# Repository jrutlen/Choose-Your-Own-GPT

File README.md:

# Choose Your Own GPT

Choose Your Own GPT is a seemingly analog device without any screens or visible digital elements. Spinning the physical dials to select characters and a story setting and then hitting the large arcade 'go' button, the built-in printer will spit out a Choose Your Own Adventure type story on the built-in receipt printer.

## Features

- Built-in 58mm thermal printer to dispense stories on demand
- Designed to be printable on 200mm² 3D printers
- Top dials can be snapped off of the main PCB to allow modification to any size
- Optional 4th dial can be added to increase story objects or add an additional element (talk like a pirate, etc.)
- Support for e-ink display (untested)
- Over-the-air (OTA) firmware updates via the web portal
- Import/export configuration as JSON

## Hardware Requirements

- ESP32 development board
- 58mm thermal printer (connected to ESP32 Serial2: RX=16, TX=17)
- Adafruit NeoPixel LEDs (WaitEnd ring: 13 LEDs on pin 26; Go button: 3 LEDs on pin 33)
- Arcade-style buttons with LEDs (Red: pin 27, Blue: pin 12, Green: pin 2, Yellow: pin 15)
- Rotary dials wired to input matrix (see PCB directory for schematic)
- 3D-printed enclosure (STL files in the `STLs` directory)
- Bill of materials in `Bill of Materials.csv`

## Building and Flashing

This project uses [PlatformIO](https://platformio.org/). All library dependencies are declared in `ChooseYourOwnGPT/platformio.ini` and are fetched automatically on first build.

1. Install [PlatformIO IDE](https://platformio.org/install) or the PlatformIO CLI.
2. Open the `ChooseYourOwnGPT` folder as a PlatformIO project.
3. Build and upload to the ESP32:
   ```
   pio run --target upload
   ```
4. You do **not** need to add your API key to the code before uploading — it is set via the web portal after the device is running.

### Library Dependencies

| Library | Version |
|---------|---------|
| Adafruit NeoPixel | 1.12.4 |
| Adafruit Thermal Printer | 1.4.1 |
| NetWizard | 1.2.0 |
| ArduinoJson | 7.3.1 |

### Building with GitHub Actions

A workflow (`.github/workflows/build.yml`) automatically builds the firmware on every push or pull request to `main`/`master` that touches `ChooseYourOwnGPT/` or the workflow file itself. No local toolchain is required to produce a flashable binary.

**What the workflow does:**
1. Checks out the repository.
2. Installs PlatformIO via `pip`.
3. Runs `pio run` inside `ChooseYourOwnGPT/`.
4. Uploads the compiled binaries as a `firmware` artifact:
   - `firmware.bin` — application image
   - `bootloader.bin` — ESP32 bootloader
   - `partitions.bin` — partition table

**Downloading the artifact:**
1. Go to the **Actions** tab of the repository on GitHub.
2. Click the latest successful **Build Firmware** run.
3. Scroll to the **Artifacts** section at the bottom and download `firmware`.
4. Unzip the archive to get the `.bin` files.

**Flashing the downloaded firmware:**

To flash from scratch (first time or full reflash), use `esptool.py`:
```
esptool.py --chip esp32 --baud 921600 \
  write_flash \
  0x1000  bootloader.bin \
  0x8000  partitions.bin \
  0x10000 firmware.bin
```

To update an already-running device, use the OTA firmware update in the web portal — see [OTA Firmware Update](#ota-firmware-update) below.

## First-Time Setup

1. Power on the device. It will start a Wi-Fi access point named **`ChooseYourOwnGPT`** with the password **`itMightBeMagic`**.
2. Connect to that network from your phone or computer.
3. A captive portal will open automatically (or navigate to `http://192.168.4.1`).
4. Enter your home Wi-Fi credentials and save. The device will reboot and connect to your network.

## Configuration

Once the device is connected to your Wi-Fi network, open a browser and go to:

```
http://<device-ip>/config
```

The device IP is printed to the serial console on connection. The configuration portal lets you adjust all settings without reflashing.

### General Settings

| Setting | Description |
|---------|-------------|
| **OpenAI API Key** | Your `sk-…` key from [platform.openai.com](https://platform.openai.com/api-keys). Stored on the device only — never sent anywhere except the OpenAI API. |
| **OpenAI Model** | The model to use for story generation (default: `gpt-4o`). |
| **Hyphenate long words** | When enabled, words that are too long for a line are broken with a hyphen instead of overflowing. |

### Character Names (Small Dial)

Up to **10** character names can be assigned to positions on the small dial. Each position corresponds to a dial setting (0–9). Names can include relationship context (e.g. `"Mia (a 7-year-old girl)"`), which is passed directly to the story prompt.

### Adventure Destinations (Large Dial)

Up to **16** adventure destinations can be assigned to positions on the large dial. Each entry is a sentence fragment appended to the story prompt (e.g. `" who go on an adventure in the Amazon Rainforest."`).

### Story Prompts

These fields control the text sent to the OpenAI API at each stage of the story:

| Field | Description |
|-------|-------------|
| **Story Prompt** | Opening prompt prepended before the selected character names. |
| **Instructions** | Instructions appended after the adventure destination (formatting rules, chapter length, button options, etc.). |
| **Surprise Ending Prompt** | Sent when the red button is pressed to request an unexpected ending. |
| **Blue Button – Continue** | Message sent when the blue button is pressed to continue the story. |
| **Blue Button – Final Chapter** | Message sent when the blue button is pressed in the final chapter. |
| **Yellow Button – Continue** | Message sent when the yellow button is pressed to continue the story. |
| **Yellow Button – Final Chapter** | Message sent when the yellow button is pressed in the final chapter. |

### Import / Export

Use the **Export Settings JSON** button to download all current settings as a `cyogpt-config.json` file. Use **Import Settings JSON** to restore or share a configuration.

### OTA Firmware Update

The `/config` portal includes a firmware update section. Select a compiled `.bin` file (from `pio run` build output) and click **Upload Firmware**. The device will reboot automatically after a successful update.

## Usage

1. Power on the device and wait for it to connect to Wi-Fi (the LEDs will indicate status).
2. Spin the **small dial** to select a character and the **large dial** to choose an adventure destination.
3. Press the **green Go button** to generate a story. The printer will output the first chapter.
4. At the end of each chapter, press the **blue** or **yellow** button to choose how the story continues.
5. Press the **red button** at any point to trigger a surprise ending.
6. After the final (5th) chapter, the story is complete. Set the dials and press Go to start a new story.

## Network Printing

The device also works as a simple network printer. It listens on TCP port **9100** and forwards every byte it receives, unchanged, to the thermal printer. A job ends when the client closes the connection or sends nothing for 3 seconds. After each job the printer's text formatting is reset, so stories print normally afterwards.

Jobs are handled between story steps. While a chapter is generating or printing, the sender waits until the device is free.

Quick test from any machine on the network:
```
echo "Hello from the network" | nc -q 5 <device-ip> 9100
```

### Python client

`clients/python/cyogpt_printer.py` is a single-file client that builds the printer's command bytes. Plain text and ASCII-art glyphs need only the standard library. Printing images or rendering TrueType text needs [Pillow](https://pypi.org/project/pillow/) (`pip install pillow`).

```python
from cyogpt_printer import Printer

HEART = [
    ".##...##.",
    "####.####",
    "#########",
    ".#######.",
    "..#####..",
    "...###...",
    "....#....",
]

with Printer("192.168.1.50") as p:          # sent as one job when the block exits
    p.justify("C").size("L").bold().text("Hello!").bold(False).size("S")
    p.glyph(HEART, scale=6, align="C")      # ASCII-art glyph, each pixel 6x6 dots
    p.render_text("☀ 21°C ☂", font_path="/usr/share/fonts/truetype/dejavu/DejaVuSans.ttf")
    p.image("logo.png")                     # scaled to 384 px and dithered
    p.justify("L").text("Printed from a Raspberry Pi")
    p.feed(3)
```

| Method | Description |
|--------|-------------|
| `text(s)` / `write(s)` | Text with or without a newline (32 chars per line at size S, encoded as CP437) |
| `bold()`, `underline(0-2)`, `inverse()`, `size('S'/'M'/'L')`, `justify('L'/'C'/'R')`, `line_height(dots)` | Text styles |
| `feed(n)` | Feed *n* lines |
| `glyph(rows, scale, align)` | Print ASCII-art (`#` = black) as a bitmap |
| `bitmap(w, h, data, align)` | Print a raw 1-bit bitmap (MSB-first rows, 1 = black, max 384 px wide) |
| `image(path_or_pil, align)` | Print an image (needs Pillow) |
| `render_text(s, font_path, font_size, align)` | Draw any Unicode text or symbol with a font (needs Pillow) |
| `raw(bytes)` | Send arbitrary printer command bytes |

It can also be run from the command line:
```
python cyogpt_printer.py <device-ip> "Some text" --center --size M
python cyogpt_printer.py <device-ip> --image photo.jpg
```

> Anyone on your local network can print to the device. There is no authentication.

### Idle LEDs

While the box waits for a story, its dial LEDs breathe. A device that borrows the printer can switch that off, say while the box stands in a dark room as part of something else, and back on again:

```
curl -X POST http://<device-ip>/api/leds -d '{"idle": false}'   # dark while idle
curl -X POST http://<device-ip>/api/leds -d '{"idle": true}'    # breathing again
curl http://<device-ip>/api/leds                                 # {"idle":true}
```

Turning a dial still lights its LED, and a story runs exactly as usual. The setting is not saved: the box always starts with the LEDs on.

## Related

Build log with photos

[Hackaday.io](https://hackaday.io/project/192751-choose-your-own-gpt)

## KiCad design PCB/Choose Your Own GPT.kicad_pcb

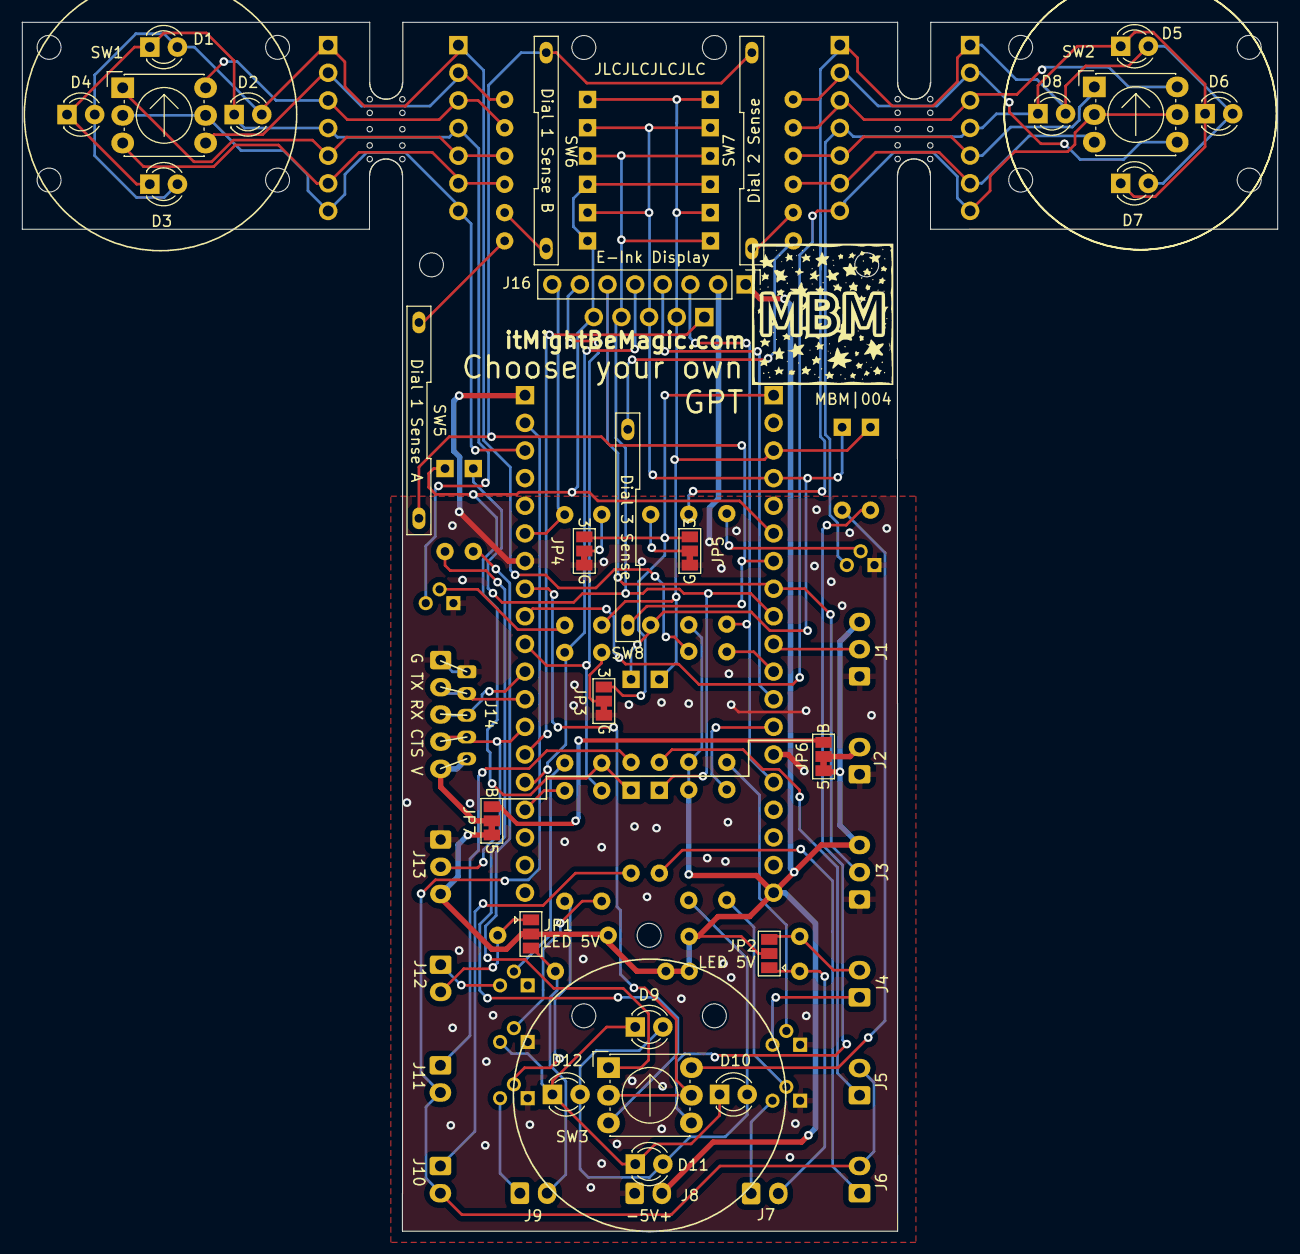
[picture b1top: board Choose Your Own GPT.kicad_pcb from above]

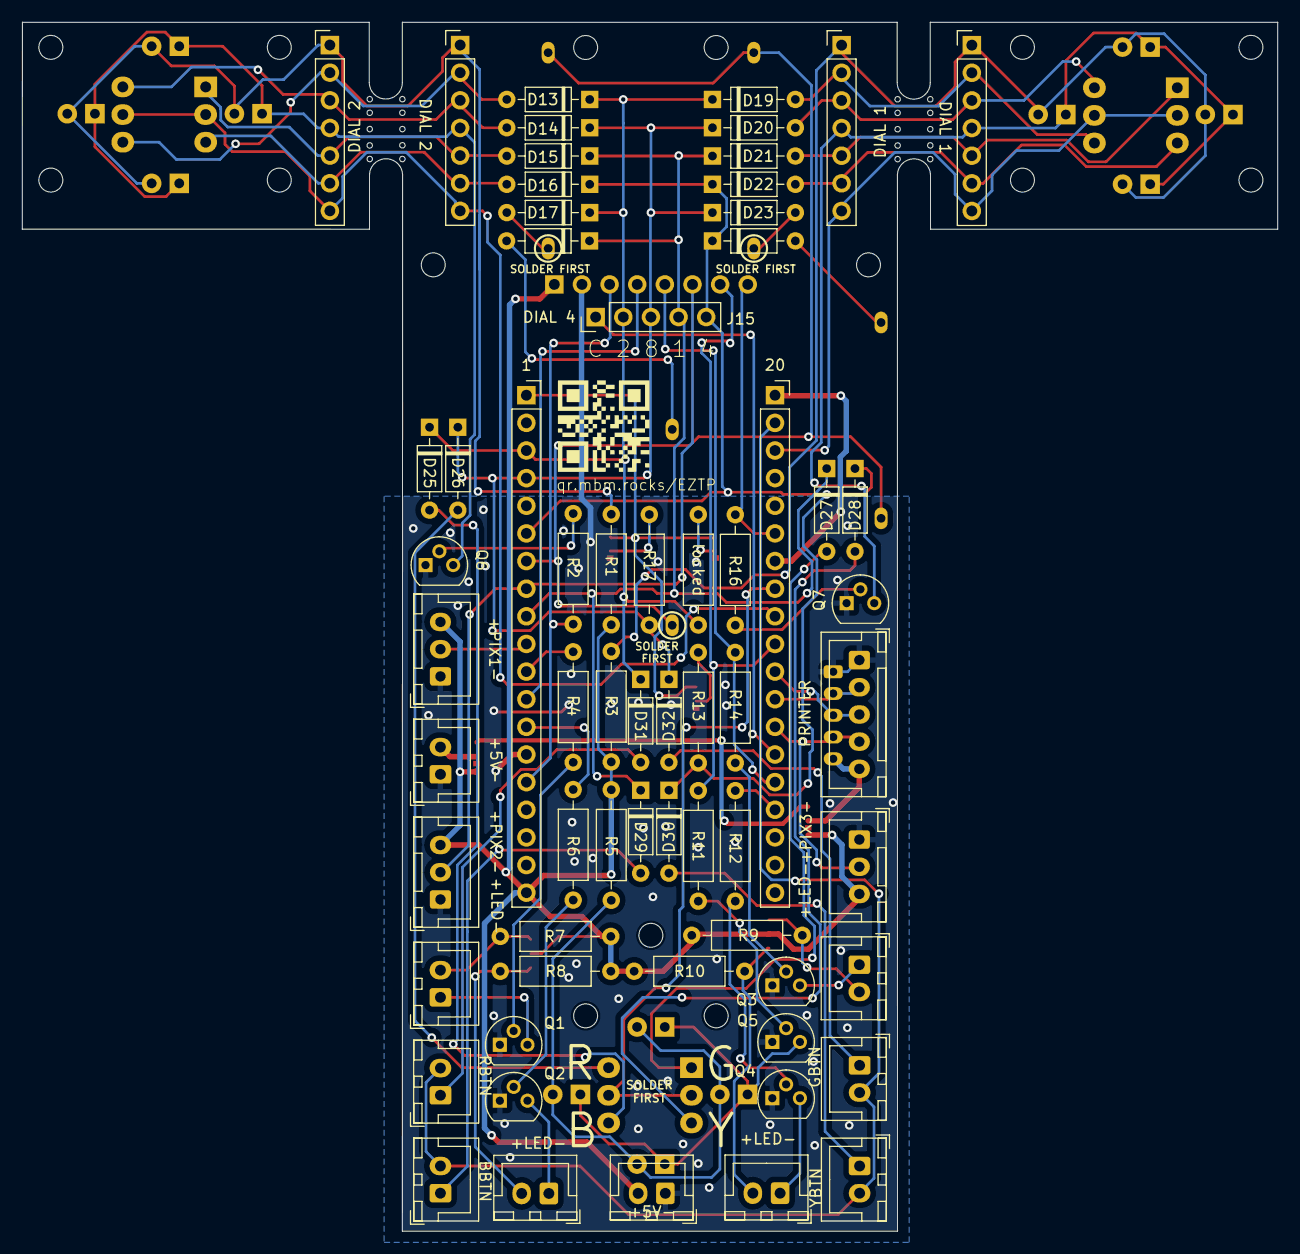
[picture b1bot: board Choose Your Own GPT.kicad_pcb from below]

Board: 2 copper layers, 115.4 x 111.1 mm, 97 parts (67 on the bottom side), 35 nets.

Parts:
1, 20: PinSocket_1x19_P2.54mm_Vertical
D1, D2, D3, D4, D5, D6, D7, D8, D9, D10, D11, D12: LED_D3.0mm
D13, D14, D15, D16, D17, D18, D19, D20, D21, D22, D23, D24, D25, D26, D27, D28, D29, D30, D31, D32: D_DO-35_SOD27_P7.62mm_Horizontal
DIAL 1, DIAL 1#2, DIAL 2, DIAL 2#2: PinHeader_1x07_P2.54mm_Vertical
J1, J3, J13: JST_XH_B3B-XH-A_1x03_P2.50mm_Vertical
J2, J4, J5, J6, J7, J8, J9, J10, J11, J12: JST_XH_B2B-XH-A_1x02_P2.50mm_Vertical
J14: JST_PH_B5B-PH-K_1x05_P2.00mm_Vertical
J14#2: JST_XH_B5B-XH-A_1x05_P2.50mm_Vertical
J15: PinHeader_1x05_P2.54mm_Vertical
J16: PinHeader_1x08_P2.54mm_Vertical
JP1, JP2: SolderJumper-3_P1.3mm_Open_Pad1.0x1.5mm
JP3, JP4: SolderJumper-3_P1.3mm_Bridged12_Pad1.0x1.5mm_NumberLabels
JP5, JP6, JP7: SolderJumper-3_P1.3mm_Bridged12_Pad1.0x1.5mm_Numb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; SolderJumper-3_P1.3mm_Bridged12_Pad1.0x1.5mm_NumberLabels
MBM|004: MBM Logo
Q1, Q2, Q3, Q4, Q5, Q6, Q7: TO-92
R1, R3, R5: 22; R_Axial_DIN0207_L6.3mm_D2.5mm_P10.16mm_Horizontal
R2, R11, R16: 390; R_Axial_DIN0207_L6.3mm_D2.5mm_P10.16mm_Horizontal
R4, R6, R12, R14: 1.7k; R_Axial_DIN0207_L6.3mm_D2.5mm_P10.16mm_Horizontal
R7, R8, R9, R10: R_Axial_DIN0207_L6.3mm_D2.5mm_P10.16mm_Horizontal
R13, R17: 4.7k; R_Axial_DIN0207_L6.3mm_D2.5mm_P10.16mm_Horizontal
SW1, SW2, SW3: Nidec_Copal_SH-7010C
SW5, SW6, SW7, SW8: Magnetic Reed Switch
locked: 4.7k; R_Axial_DIN0207_L6.3mm_D2.5mm_P10.16mm_Horizontal
mouse-bite-3mm-slot, mouse-bite-3mm-slot#2: VAL**; My MouseBite
qr.mbm.rocks/EZTP: LOGO

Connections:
3v3: 1.1, JP3.3, JP4.3, JP5.3
5V: 1.19, J1.3, J2.2, J3.3, J8.2, J13.3, J14.5, J14#2.5, J16.1, JP1.2, JP2.2, JP6.1, JP6.2, JP7.1, JP7.2, R1.2, R3.2, R5.1, R7.2, R8.2, R9.1, R10.1
BLED: 1.12, Q2.2, R6.1, R6.2
BLL-: J7.1, Q2.3
BTNC: 20.23, J5.2, J6.2, J10.2, J11.2
D1C: 20.22, DIAL 1.7, DIAL 1#2.7, SW1.C
D1GND: D1.1, D2.1, D3.1, D4.1, DIAL 1.4, DIAL 1#2.4, Q7.3
D1LED: 20.21, J16.BUSY, Q7.2, R16.1, R16.2
D2C: 20.18, DIAL 2.7, DIAL 2#2.7, SW2.C
D2GND: D5.1, D6.1, D7.1, D8.1, DIAL 2.4, DIAL 2#2.4, Q6.3
D2LED: 1.13, J16.MOSI, Q6.2, R2.1, R2.2
D3C: 20.19, SW3.C
D3GND: D9.1, D10.1, D11.1, D12.1, Q5.3
D3LED: 20.5, J16.RST, Q5.2, R11.1, R11.2
D3SEN: 1.14, J16.SCK
D4C: 20.0, J15.1
DSC: 1.32, SW5.2, SW6.2, SW7.2, SW8.2
GLED: 20.15, J16.CS, Q3.2, R14.1, R14.2
GND: 20.1, 20.7, J1.1, J2.1, J3.1, J8.1, J13.1, J14.1, J14#2.1, J16.2, JP3.1, JP4.1, JP5.1, Q1.1, Q2.1, Q3.1, Q4.1, Q5.1, Q6.1, Q7.1
GNL-: J12.1, Q3.3
JUMP: JP6.3, JP7.3
LED+: D1.2, D2.2, D3.2, D5.2, D6.2, D7.2, D9.2, D10.2, D11.2, DIAL 1.1, DIAL 1#2.1, DIAL 2.1, DIAL 2#2.1, J4.2, J7.2, J9.2, J12.2, JP1.1, JP1.3, JP2.1, JP2.3, R1.1, R3.1, R5.2, R7.1, R8.1, R9.2, R10.2
NEO1: 1.26, J1.2
NEO2: 1.33, J3.2, J16.DC
NEO3: 20.4, J13.2, J14.4, J14#2.4
RDL-: J4.1, Q1.3
RLED: 1.27, Q1.2, R4.1, R4.2
RX2: 20.17, J14.3, J14#2.3
SEL1: 1.25, D15.1, D15.2, D18.1, D18.2, D21.1, D21.2, D27.1, D27.2, D29.1, D29.2, DIAL 1.5, DIAL 1#2.5, DIAL 2.5, DIAL 2#2.5, J6.1, J15.4, SW1.1, SW2.1, SW3.1, SW8.1
SEL2: 1.36, D13.1, D13.2, D17.1, D17.2, D19.1, D19.2, D25.1, D25.2, D31.1, D31.2, DIAL 1.2, DIAL 1#2.2, DIAL 2.2, DIAL 2#2.2, J5.1, J15.2, JP4.2, SW1.2, SW2.2, SW3.2, SW7.1, locked.1, locked.2
SEL4: 1.35, D16.1, D16.2, D22.1, D22.2, D24.1, D24.2, D28.1, D28.2, D30.1, D30.2, DIAL 1.6, DIAL 1#2.6, DIAL 2.6, DIAL 2#2.6, J10.1, J15.5, JP3.2, R13.1, R13.2, SW1.4, SW2.4, SW3.4, SW5.1
SEL8: 1.39, D14.1, D14.2, D20.1, D20.2, D23.1, D23.2, D26.1, D26.2, D32.1, D32.2, DIAL 1.3, DIAL 1#2.3, DIAL 2.3, DIAL 2#2.3, J11.1, J15.3, JP5.2, R17.1, R17.2, SW1.8, SW2.8, SW3.8, SW6.1
TX2: 20.16, J14.2, J14#2.2
YLED: 20.2, Q4.2, R12.1, R12.2
YWL-: J9.1, Q4.3

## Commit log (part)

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2023-09-29 Initial Commit
    Added PCB files
2023-10-19 Add 3D Files
2025-03-07 Initial Code Release
2025-11-26 Initial plan
2025-11-26 Add comprehensive error handling and fix syntax errors
2025-11-26 Add documentation and library comments for best practices
2025-11-26 Final documentation and security review completed
2025-11-29 Add web portal configuration for dial variables, prompts, and GitHub Actions build workflow
2025-11-29 Update documentation with configuration instructions and GitHub Actions info
2025-11-29 Fix security issues: API key handling and WiFi password documentation
2025-11-29 Fix GitHub Actions security: add explicit GITHUB_TOKEN permissions
2025-11-29 Update enhancement suggestions in MAINTENANCE.md
    OTA updates already exist
2025-12-02 Update platform version and clean up library dependencies
    Put version back to 51.3.3
2025-12-02 Update platform URL for espressif32
    Pin to version 51.03.03
2025-12-02 Remove redundant printer wake checks
2026-04-13 Add web configuration portal, remove MQTT, clean up codebase
    - Add config.h/config.cpp: Persistent configuration using ESP32 NVS (Preferences)
    with defaults for model, API key, names, adventures, and all prompts
    - Add web_portal.h/web_portal.cpp: Web-based config UI at /config with JSON API
    endpoints for get/save/reset configuration
    - Rewrite main.cpp: Remove unused MQTT parameters, remove credentials.h dependency,
    integrate config system, fix missing comma bug in adventureNames array,
2026-04-13 Address code review: increase buffer sizes, extract magic delay constant
    Agent-Logs-Url: https://github.com/jrutlen/Choose-Your-Own-GPT/sessions/21a72f1f-565d-41af-bef8-21e4059ad3f0
2026-04-14 Add GitHub Actions CI build workflow
    - Update platformio.ini to use pioarduino URL (espressif32@51.3.3 is not in
    the standard PlatformIO registry; the direct ZIP URL resolves correctly in CI)
    - Add .github/workflows/build.yml: installs PlatformIO, caches packages,
    builds firmware, and uploads firmware.bin/bootloader.bin/partitions.bin
    as a build artifact
    Agent-Logs-Url: https://github.com/jrutlen/Choose-Your-Own-GPT/sessions/ee2da09b-cae2-4e4f-9b2f-4dcccc2c1f16
2026-04-14 Fix /config not loading after WiFi connects
    Two bugs prevented the config page from being served:
    1. webPortalSetup() and server.begin() were called after NW.autoConnect().
    In the captive-portal path (first boot), NetWizard calls server.begin()
    internally, then WiFi.mode(WIFI_STA) tears down the AP interface.
    Because NetWizard leaves the internal _server handle non-null,
    the sketch's later server.begin() hits the early-return guard and is
2026-04-14 Fix bootloop: move server.begin() after autoConnect
    Calling server.begin() before NW.autoConnect() (the previous fix) triggers
    lwIP's "Invalid mbox" assert crash-loop because the TCP/IP task mailbox does
    not exist until WiFi.begin() is called inside autoConnect.
    Fix: keep webPortalSetup() before autoConnect (routes registered here
    survive NetWizard's _stopHTTP() which only removes its own handlers), but
    move server.begin() back to after autoConnect so it runs only after the
2026-04-14 Fix /config page going unreachable: remove NW.loop(), restart server on reconnect
    NW.loop() was calling _stopHTTP() (portal cleanup timeout) after ~3 minutes,
    which stopped the WebServer socket and made /config unreachable. Since we use
    NetWizardStrategy::BLOCKING, the entire portal session is handled inside
    autoConnect(); NW.loop() is not needed afterward. WiFi reconnection is
    handled natively by the ESP32 WiFi stack.
    Changes:
2026-04-14 Fix state machine after story completion
    - State 3: sync dial[] with freshly-read lastDial[] to prevent stale
    values causing immediate false dialSet triggers that detach dial LED
    pins from the LEDC PWM channel and break the fade animation
    - resetHardwareState: replace global ChatGPTuino instance with
    std::unique_ptr; reassigning the pointer destroys the old object and
    creates a fresh one with _msgCount=0, clearing the previous story's
2026-04-14 Restore logo, add OTA update and import/export to config portal
    - Logo: restore original style (size M, bold+inverse, dashes, centred)
    - Config portal: add Import/Export JSON section (client-side FileReader
    + fetch; exports download as cyogpt-config.json)
    - Config portal: add OTA Firmware Update section; POST to /ota/update
    streams binary to flash via Update library; static s_otaFailed flag
    preserves error across abort() boundary; flush()+delay before reboot
2026-04-15 Fix crash and model incompatibility with newer OpenAI models
    - Bundle ChatGPTuino locally in lib/ChatGPTuino/ with two fixes:
    - max_tokens → max_completion_tokens (required by gpt-5.x, o1, o3, etc.)
    - null-safe content check in putResponseInMsgArray: logs the API error
    string and returns 0 instead of calling strlen(nullptr) → hard fault
    - Add error.message to JSON filter for API error visibility
    - Remove external ChatGPTuino git dep from platformio.ini
2026-04-15 Implement word-wrap for thermal printer output
    Agent-Logs-Url: https://github.com/jrutlen/Choose-Your-Own-GPT/sessions/8d34b501-e6f2-402c-bc0e-b4e2d35bc39c
2026-04-16 Add hyphenation mode toggle to config page
    Agent-Logs-Url: https://github.com/jrutlen/Choose-Your-Own-GPT/sessions/e4be828c-5c22-45e4-90e1-3f08c34517dc
2026-04-16 Fix String(pad, ' ') padding bug in printWrapped
    Agent-Logs-Url: https://github.com/jrutlen/Choose-Your-Own-GPT/sessions/f6c8bc03-c79f-4345-bd20-97f95ce14ab0
2026-04-16 Disable printer.wake() calls
    Comment out printer.wake() to prevent printing 8
2026-04-20 docs: update README with usage and configuration instructions
    Agent-Logs-Url: https://github.com/jrutlen/Choose-Your-Own-GPT/sessions/a258fdf8-6eaa-4a11-bde5-ffe6b94fbe63
2026-04-20 docs: add GitHub Actions build instructions to README
    Agent-Logs-Url: https://github.com/jrutlen/Choose-Your-Own-GPT/sessions/7bd835b6-0315-41a8-b944-ba8e47fac2d0
